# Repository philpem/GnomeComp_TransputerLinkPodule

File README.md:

# Recreation of Gnome Computers Transputer Podules

Phil Pemberton, Feb-Apr 2026.

This is a recreation of the Transputer Link and TRAM Podules by Gnome Computers Ltd.

For the Link card, I initially recreated the PROM contents and PAL equations from the schematic. I fixed these when Chris sent me the originals from his archives.

Thanks are due to Chris Stenton of the former Gnome Computers Ltd., who graciously dug into his archives to find some blank PCBs and the PAL/PROM programming files, which were used to build this.

## Files included

  * `doc/*`: Documentation in GCAL and PDF format.
  * `LinkAdapter/*`: KiCAD schematic and PCB and programming files for the Link Adapter.
  * `kobold.c`: Kobold, a brutish licence key forger for Gnome's Transputer `afserver`, `nbserver`, `m2server` and `server14` iservers. Included for documentary, and historical preservation purposes only.

### Gnome Transputer product licensing

The Gnome port of the standard Inmos `iserver` seems to have no licence checks.

The other Transputer host servers (`afserver`, `nbserver`, `m2server` and `server14`) have licensing which is based on the Podule serial number.

The Podule serial number is stored in the second and third bytes of the Podule ID PROM: `serial = (rom[1] >> 4) + (rom[2] << 4)`. The low nibble of `rom[1]` must remain at zero.

From here, you can use Kobold to generate licence keys:

```
$ gcc -o kobold kobold.c

$ ./kobold
Usage: ./kobold [-p PRODUCT] [ -d HEX_KEY_TO_DECRYPT | -e SERIAL_NUMBER [-s STARTING_KEY] ]

Kobold decrypts and finds Podule keys for Gnome Computers Transputer products.

Use -pN to select the product:
   0: afserver, nbserver, m2server (default)
   1: server14

May Kurtulmak bless your fingertips!

# Generate random product keys for serial number 69
$ ./kobold -p0 -e47
Serial 69 (0x45) for afserver/m2server/nbserver => Key 313a5167
$ ./kobold -p1 -e47
Serial 69 (0x45) for server14 => Key 2f51eee5

# Generate product keys starting from a certain value
$ ./kobold -p1 -e69 -s55aa55aa
Serial 69 (0x45) for server14 => Key 55aa798a

# Decrypt product keys
$ ./kobold -p1 -d55aa798a
Key 55aa798a for server14 => serial 69 (0x45)
```

The keys you've generated need to go in `$.library.keys` on the drive you have selected when you run the `*server`. **Note that the Gnome tools only check the first 20 keys in the file!**.

#### Some notes on the algorithm

The algorithm used is a one-way function which contains a linear-congruential-generator-like structure. Both the multiplicative constants are prime, and the additive constant is the same for all the `iserver`s. The multiplied output and adder output are XORed together to produce an accumulator value. A compression function picks three spaced-out 3-bit values from the accumulator: these are used to select three 4-bit numbers which are used to generate the final result. This result needs to match the serial number of the card for the licence to be considered valid.

I'd tell you why the key finder was called Kobold, but explaining a joke would kill it. If you don't get the reference, assume it means something like "Kobold Outputs Benign Obviously-Legal Data". For educational purposes only, not for use in the State of Delaware, void where prohibited, may cause cancer if operated in the State of California.

## About GCAL

The documents for Gnome products were prepared using the University of Cambridge GCAL system, developed by Philip Hazel and [mentioned in his autobiography](https://gwern.net/doc/cs/algorithm/2017-hazel.pdf#page=48) (and very few other places).

GCAL had a successor, SGCAL, which is similarly lightly documented on the public internet. The [source code to version 1.33](https://web.archive.org/web/20151030064313/https://www-uxsup.csx.cam.ac.uk/~bjh21/sgcal_1.33.orig.tar.gz) is preserved, but precious little else. I haven't tried to use SGCAL.

The GCAL manual is preserved in the `doc` directory, and has been converted to PDF format.

Unsurprisingly, [GCAL output is supported by the Aspic utility](https://manpages.ubuntu.com/manpages/trusty/man1/aspic.1.html), which converts a text description of an line-art graphic into EPS, SVG or GCAL line-art.

### Podule ID PROMs

The Podule ID on the various cards is an 8-byte old-style ID (not an ECID) and decodes as follows:

```
0:  &00  - (&01 if generating IRQ)
1:  (reserved)
2:  (reserved)
3:  &24  - Product type low
4:  &00  - Product type high
5:  &0E  - Manufacturer low
6:  &00  - Manufacturer high
7:  &00  - Country code
```

The PAL data seems to use A3 to indicate FIQ status (1=FIQ active), but the Link Podule doesn't use FIQs. A4 is similarly used to indicate IRQs.

There are also two bytes programmed in locations 1 and 2 which are the same in every copy. These areas are marked Reserved in the Podule specification, so should be programmed to zero!
This data seems to be the card's serial number.

The image from Gnome is identified by their `TPROD` utility as having serial number 47, which is encoded into the second and third bytes of the Podule ID PROM:

```
0000: 00 f0 02 24 00 0e 00 00
0008: 04 f0 02 24 00 0e 00 00
0010: 01 f0 02 24 00 0e 00 00
0018: 05 f0 02 24 00 0e 00 00
         ^  ^^

Serial number 47 = &2F => stored in the upper 12 bits of a ui16le at prom[1].

This leaves bits W[1:0] (code width), IS (interrupt status relocation) and CD (chunks present) clear.
```

These are then converted into licence keys or "Podule keys" which are checked by `afserver`, `nbserver` and `Server14`, and can be generated with Kobold (see above).

#### Product type codes

  * `&24`: Link Adapter
  * `&4B`: TRAM Motherboard

Other than the product ID and serial number, the Link and TRAM cards have identical PROM contents.

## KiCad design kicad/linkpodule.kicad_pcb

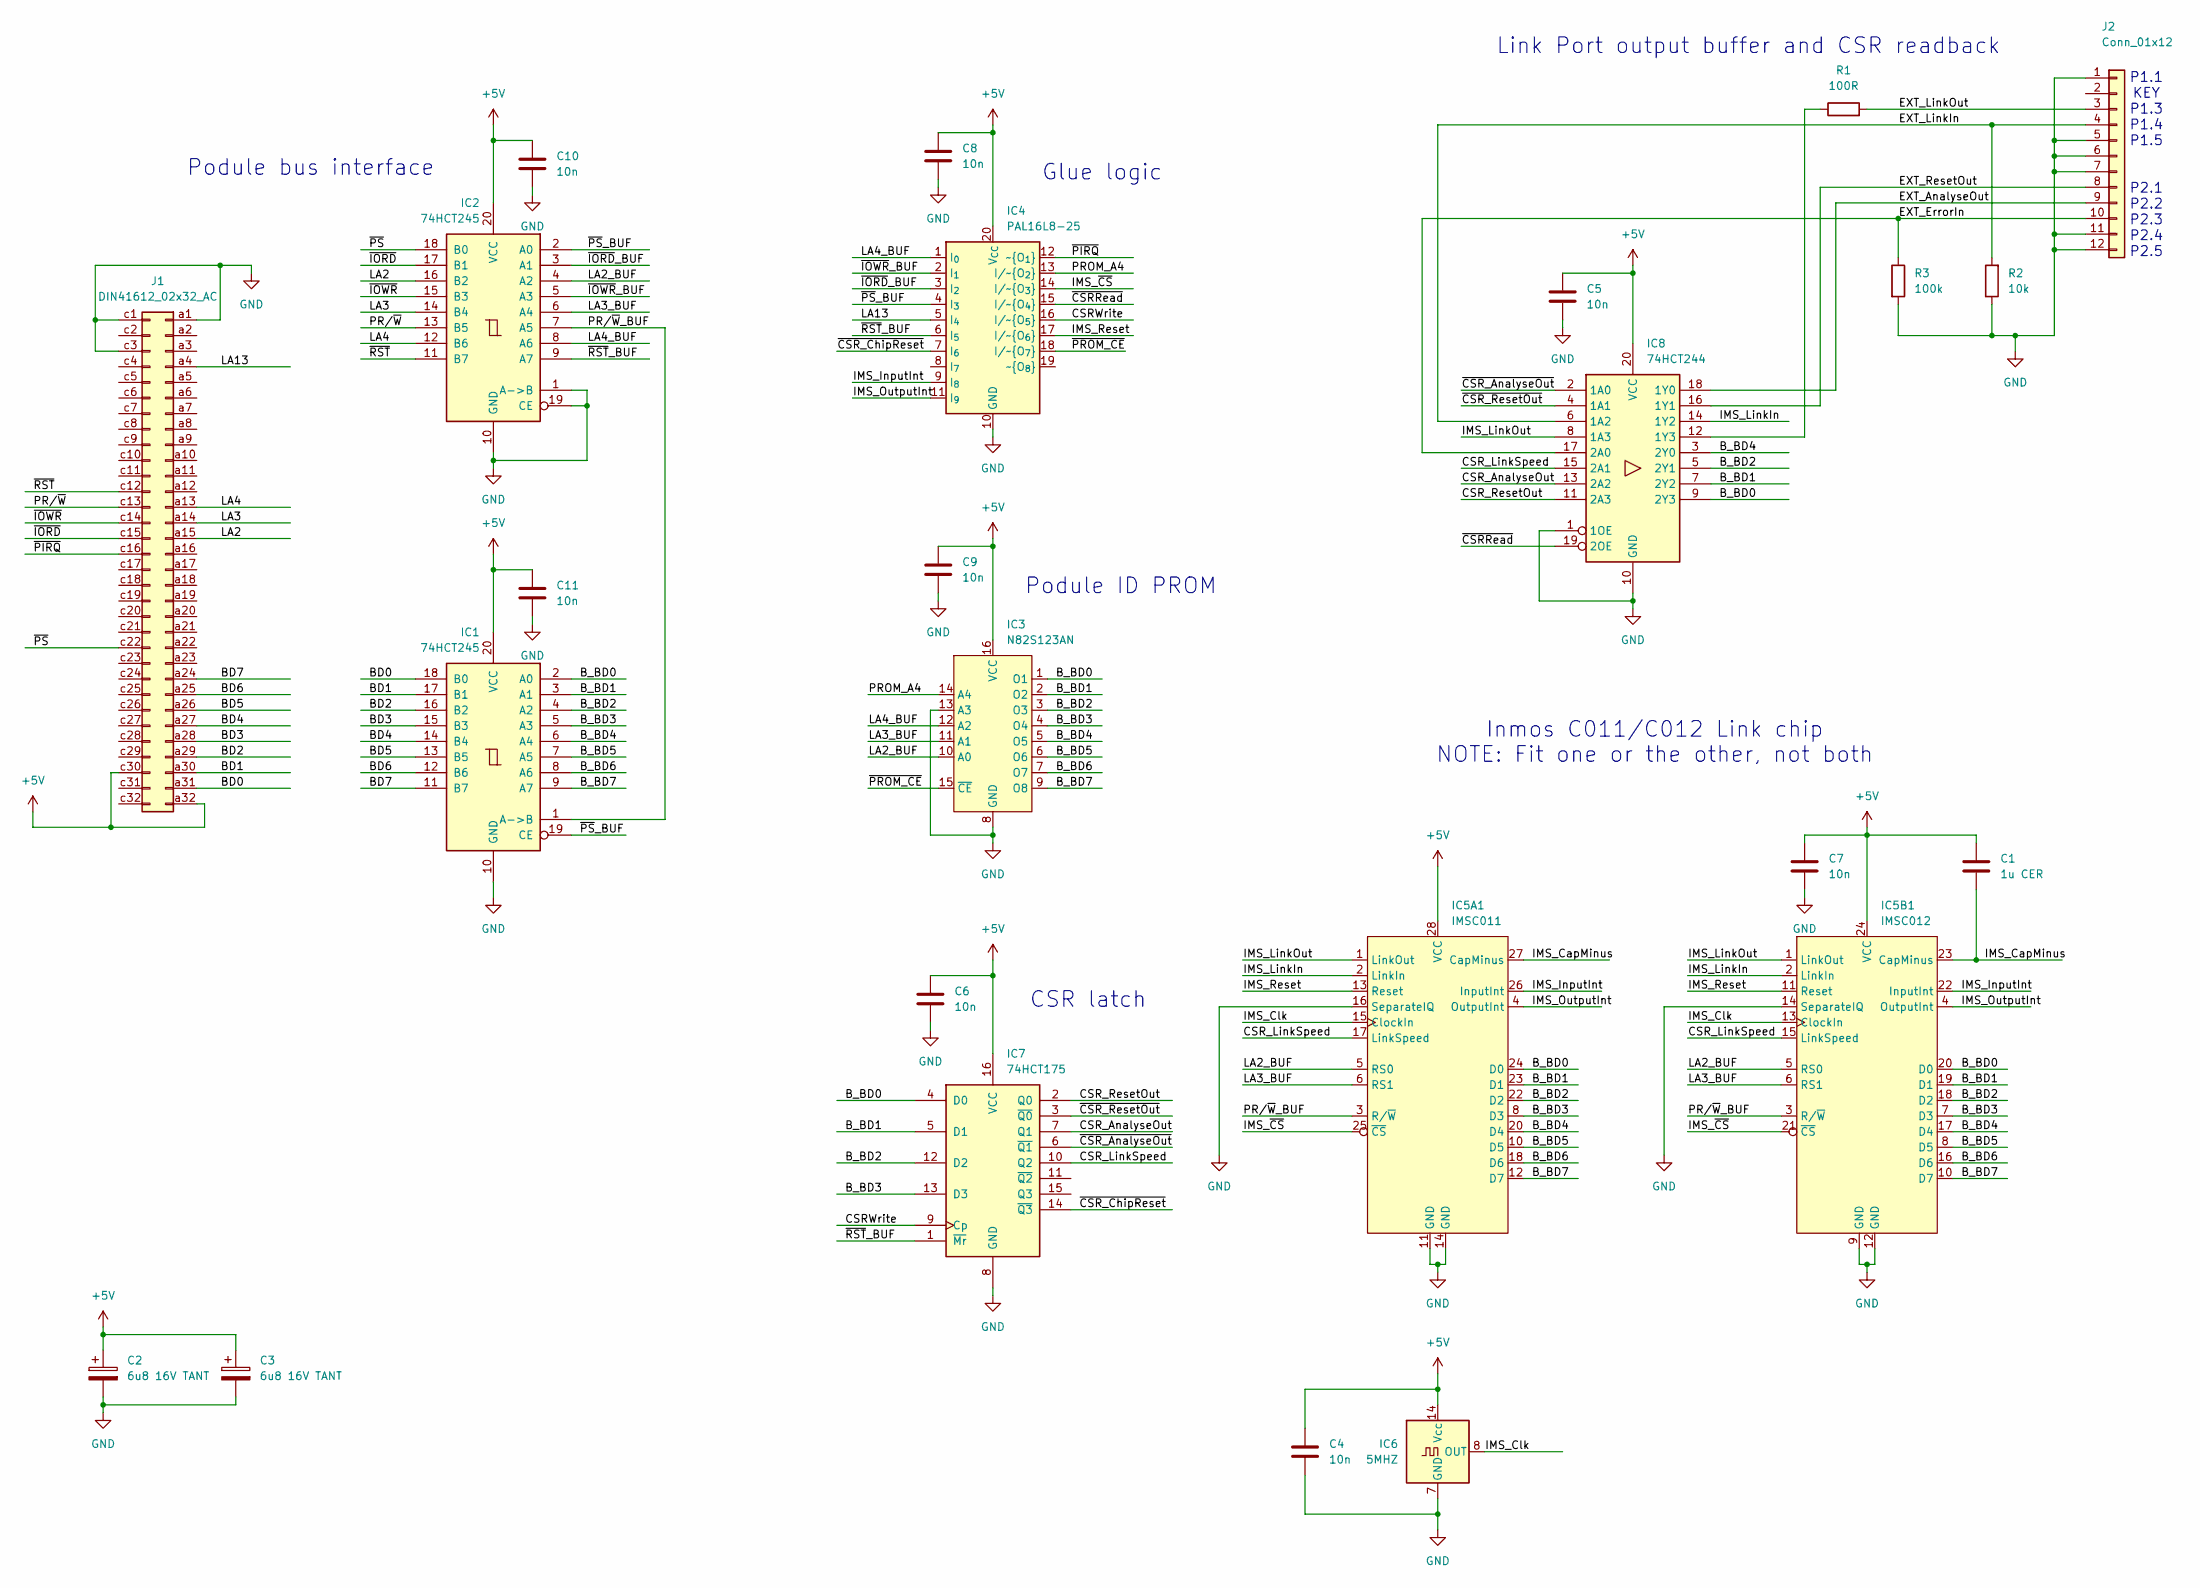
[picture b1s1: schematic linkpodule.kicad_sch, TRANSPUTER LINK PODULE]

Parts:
C1: 1u CER; C_Disc_D4.3mm_W1.9mm_P5.00mm
C2, C3: 6u8 16V TANT; CP_Radial_Tantal_D8.0mm_P5.00mm
C4, C5, C6, C7, C8, C9, C10, C11: 10n; C_Disc_D4.3mm_W1.9mm_P5.00mm
IC1, IC2: 74HCT245; DIP-20_W7.62mm
IC3: N82S123AN; DIP-16_W7.62mm
IC4: PAL16L8-25; DIP-20_W7.62mm
IC5A1: IMSC011; DIP-28_W15.24mm
IC5B1: IMSC012; DIP-24_W7.62mm
IC6: 5MHZ; Oscillator_DIP-14
IC7: 74HCT175; DIP-16_W7.62mm
IC8: 74HCT244; DIP-20_W7.62mm
J1: DIN41612_02x32_AC; DIN41612_C_2x32_Male_Horizontal_THT
J2: Conn_01x12; PinHeader_1x12_P2.54mm_Horizontal
R1: 100R; R_Axial_DIN0207_L6.3mm_D2.5mm_P10.16mm_Horizontal
R2: 10k; R_Axial_DIN0207_L6.3mm_D2.5mm_P10.16mm_Horizontal
R3: 100k; R_Axial_DIN0207_L6.3mm_D2.5mm_P10.16mm_Horizontal

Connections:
+5V: C1.1, C2.1, C3.1, C4.1, C5.1, C6.1, C7.1, C8.1, C9.1, C10.1, C11.1, IC1.20 (VCC), IC2.20 (VCC), IC3.16 (VCC), IC4.20 (V_{CC}), IC5A1.28 (VCC), IC5B1.24 (VCC), IC6.14 (Vcc), IC7.16 (VCC), IC8.20 (VCC), J1.a32, J1.c30
/BD0: IC1.18 (B0), J1.a31
/BD1: IC1.17 (B1), J1.a30
/BD2: IC1.16 (B2), J1.a29
/BD3: IC1.15 (B3), J1.a28
/BD4: IC1.14 (B4), J1.a27
/BD5: IC1.13 (B5), J1.a26
/BD6: IC1.12 (B6), J1.a25
/BD7: IC1.11 (B7), J1.a24
/B_BD0: IC1.2 (A0), IC3.1 (O1), IC5A1.24 (D0), IC5B1.20 (D0), IC7.4 (D0), IC8.9 (2Y3)
/B_BD1: IC1.3 (A1), IC3.2 (O2), IC5A1.23 (D1), IC5B1.19 (D1), IC7.5 (D1), IC8.7 (2Y2)
/B_BD2: IC1.4 (A2), IC3.3 (O3), IC5A1.22 (D2), IC5B1.18 (D2), IC7.12 (D2), IC8.5 (2Y1)
/B_BD3: IC1.5 (A3), IC3.4 (O4), IC4.19 (~O_{8}), IC5A1.8 (D3), IC5B1.7 (D3), IC7.13 (D3)
/B_BD4: IC1.6 (A4), IC3.5 (O5), IC5A1.20 (D4), IC5B1.17 (D4), IC8.3 (2Y0)
/B_BD5: IC1.7 (A5), IC3.6 (O6), IC5A1.10 (D5), IC5B1.8 (D5)
/B_BD6: IC1.8 (A6), IC3.7 (O7), IC5A1.18 (D6), IC5B1.16 (D6)
/B_BD7: IC1.9 (A7), IC3.9 (O8), IC5A1.12 (D7), IC5B1.10 (D7)
/CSRWrite: IC4.16 (I/~O_{5}), IC7.9 (Cp)
/CSR_AnalyseOut: IC7.7 (Q1), IC8.13 (2A2)
/CSR_LinkSpeed: IC5A1.17 (LinkSpeed), IC5B1.15 (LinkSpeed), IC7.10 (Q2), IC8.15 (2A1)
/CSR_ResetOut: IC7.2 (Q0), IC8.11 (2A3)
/EXT_AnalyseOut: IC8.18 (1Y0), J2.9
/EXT_ErrorIn: IC8.17 (2A0), J2.10, R3.1
/EXT_LinkIn: IC8.6 (1A2), J2.4, R2.2
/EXT_LinkOut: J2.3, R1.2
/EXT_ResetOut: IC8.16 (1Y1), J2.8
/IMS_CapMinus: C1.2, IC5A1.27 (CapMinus), IC5B1.23 (CapMinus)
/IMS_Clk: IC5A1.15 (ClockIn), IC5B1.13 (ClockIn), IC6.8 (OUT)
/IMS_InputInt: IC4.9 (I_{8}), IC5A1.26 (InputInt), IC5B1.22 (InputInt)
/IMS_LinkIn: IC5A1.2 (LinkIn), IC5B1.2 (LinkIn), IC8.14 (1Y2)
/IMS_LinkOut: IC5A1.1 (LinkOut), IC5B1.1 (LinkOut), IC8.8 (1A3)
/IMS_OutputInt: IC4.11 (I_{9}), IC5A1.4 (OutputInt), IC5B1.4 (OutputInt)
/IMS_Reset: IC4.17 (I/~O_{6}), IC5A1.13 (Reset), IC5B1.11 (Reset)
/IMS_~CS: IC4.14 (I/~O_{3}), IC5A1.25 (~CS), IC5B1.21 (~CS)
/LA2: IC2.16 (B2), J1.a15
/LA2_BUF: IC2.4 (A2), IC3.10 (A0), IC5A1.5 (RS0), IC5B1.5 (RS0)
/LA3: IC2.14 (B4), J1.a14
/LA3_BUF: IC2.6 (A4), IC3.11 (A1), IC5A1.6 (RS1), IC5B1.6 (RS1)
/LA4: IC2.12 (B6), J1.a13
/LA4_BUF: IC2.8 (A6), IC3.12 (A2), IC4.1 (I_{0})
/LA13: IC4.5 (I_{4}), J1.a4
/PROM_A4: IC3.14 (A4), IC4.13 (I/~O_{2})
/PR/~W: IC2.13 (B5), J1.c13
/PR/~W_BUF: IC1.1 (A->B), IC2.7 (A5), IC5A1.3 (R/~W), IC5B1.3 (R/~W)
/~CSRRead: IC4.15 (I/~O_{4}), IC8.19 (2OE)
/~CSR_AnalyseOut: IC7.6 (~Q1), IC8.2 (1A0)
/~CSR_ChipReset: IC4.7 (I_{6}), IC7.14 (~Q3)
/~CSR_ResetOut: IC7.3 (~Q0), IC8.4 (1A1)
/~IORD: IC2.17 (B1), J1.c15
/~IORD_BUF: IC2.3 (A1), IC4.3 (I_{2})
/~IOWR: IC2.15 (B3), J1.c14
/~IOWR_BUF: IC2.5 (A3), IC4.2 (I_{1})
/~PIRQ: IC4.12 (~O_{1}), J1.c16
/~PROM_CE: IC3.15 (~CE), IC4.18 (I/~O_{7})
/~PS: IC2.18 (B0), J1.c22
/~PS_BUF: IC1.19 (CE), IC2.2 (A0), IC4.4 (I_{3})
/~RST: IC2.11 (B7), J1.c12
/~RST_BUF: IC2.9 (A7), IC4.6 (I_{5}), IC7.1 (~Mr)
GND: C2.2, C3.2, C4.2, C5.2, C6.2, C7.2, C8.2, C9.2, C10.2, C11.2, IC1.10 (GND), IC2.1 (A->B), IC2.10 (GND), IC2.19 (CE), IC3.8 (GND), IC3.13 (A3), IC4.10 (GND), IC5A1.11 (GND), IC5A1.14 (GND), IC5A1.16 (SeparateIQ), IC5B1.9 (GND), IC5B1.12 (GND), IC5B1.14 (SeparateIQ), IC6.7 (GND), IC7.8 (GND), IC8.1 (1OE), IC8.10 (GND), J1.a1, J1.c1, J1.c3, J2.1, J2.5, J2.6, J2.7, J2.11, J2.12, R2.1, R3.2
unnamed: IC8.12 (1Y3), R1.1

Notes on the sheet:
Podule ID PROM
Podule bus interface
Glue logic
CSR latch
Link Port output buffer and CSR readback
Inmos C011/C012 Link chip NOTE: Fit one or the other, not both
P1.1 KEY P1.3 P1.4 P1.5 P2.1 P2.2 P2.3 P2.4 P2.5

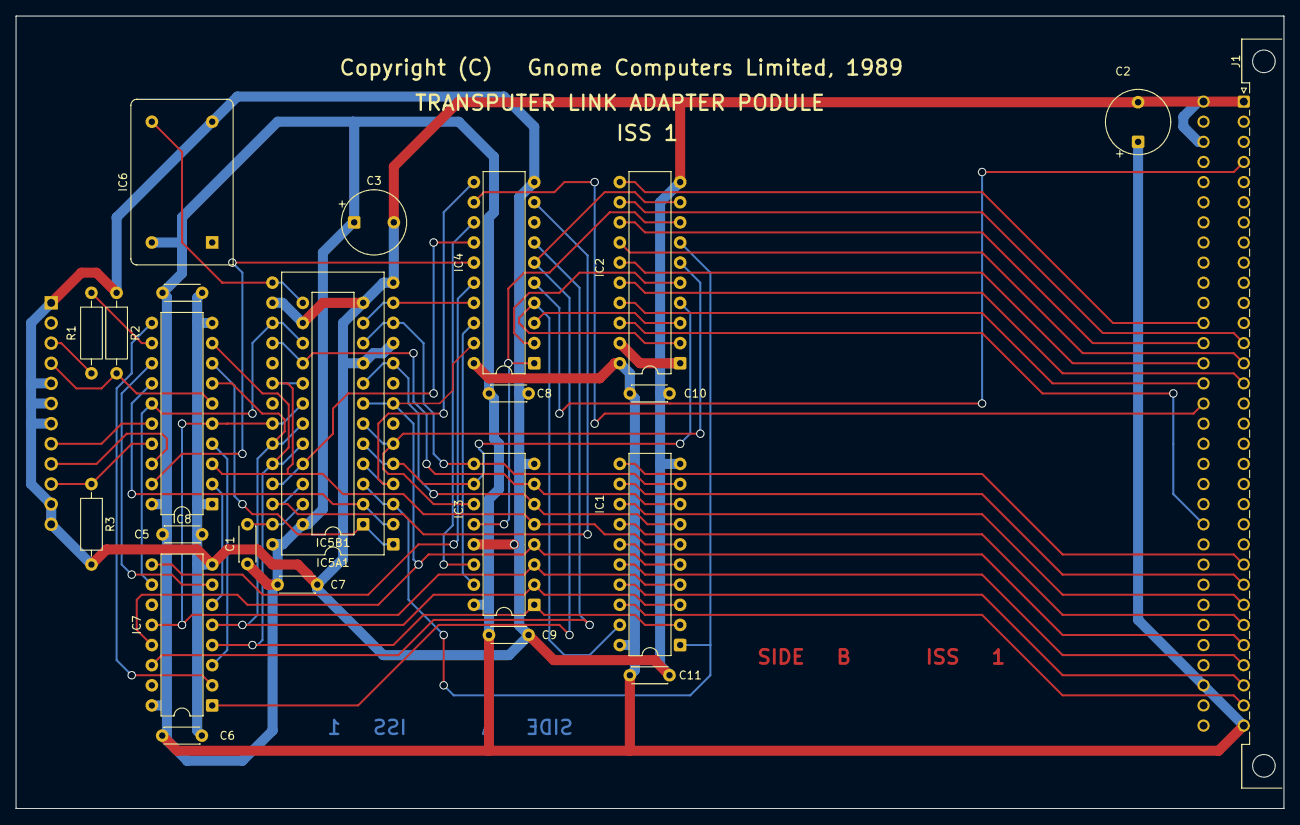
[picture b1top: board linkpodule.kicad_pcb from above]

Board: 2 copper layers, 160.0 x 100.0 mm, 25 parts (1 on the bottom side), 60 nets.

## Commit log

2026-02-23 kicad: Add missing D3 connection on PAL
2026-02-23 Add original programming files and CUPL test vectors
2026-02-23 fix perms on LAP images
2026-02-23 Update README with more details about the new files
2026-02-23 add simulator output files and GAL JEDEC with test vectors
2026-02-24 add Kobold key generator for Gnome Transputer products
2026-04-16 Move Link Adapter files into a subdirectory
2026-04-16 Add TRAM Motherboard original PALs and converted CUPL GAL source
2026-04-16 Add TRAM Podule docs
2026-04-17 update readmes for subprojects

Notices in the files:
kicad/linkpodule.kicad_pcb:
Copyright (C) Gnome Computers Limited, 1989
